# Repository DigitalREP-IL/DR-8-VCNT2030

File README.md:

This sensor board is designed around the Vishay VCNT2030, a new Vertical Cavity Surface Emitting Laser (VCSEL) short range reflective sensor.

The current-related resistors were chosen following the Vishay application note for a long distance / low reflectivity scenario. Thus, for optimal performance the board should be supplied at 5V, although the Send input is buffered by a small MOSFET with a Vgs of 1.8V.

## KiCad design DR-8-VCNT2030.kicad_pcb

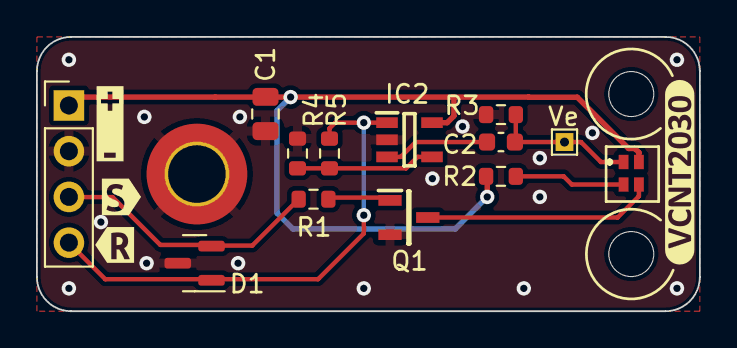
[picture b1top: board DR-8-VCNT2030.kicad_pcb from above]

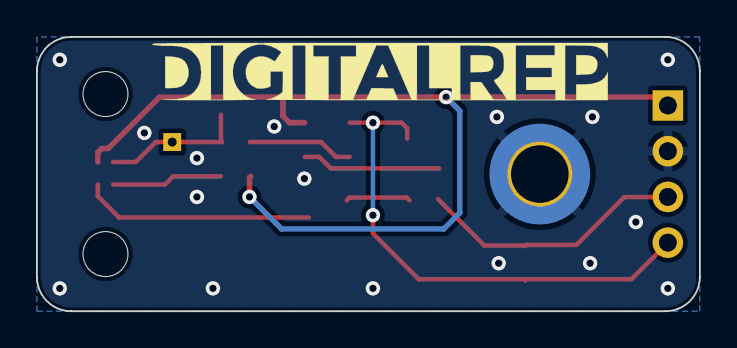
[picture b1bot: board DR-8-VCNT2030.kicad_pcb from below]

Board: 2 copper layers, 36.8 x 15.2 mm, 20 parts (2 on the bottom side), 10 nets.

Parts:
C1: C; C_0805_2012Metric
C2: C; C_0603_1608Metric
D1: SP0502BAHT; SOT-23
H1: MountingHole_Pad; MountingHole_3.2mm_M3_DIN965_Pad_TopBottom
IC1: VCNT2030
IC2: MIC6211YM5-TR; SOT95P280X145-5N
J1: Conn_01x04; PinHeader_1x04_P2.54mm_Vertical
LOGO1: Digital; digital
LOGO2: Rep; repword_soldermask
Q1: SI2302CDS-T1-GE3; SOT95P237X112-3N
R1: 100; R_0603_1608Metric
R2, R3, R4, R5: R_US; R_0603_1608Metric
TP1: Ve; TestPoint_THTPad_1.0x1.0mm_Drill0.5mm
kibuzzard-64F8F02C: G***; kibuzzard-64F8F02C
kibuzzard-64F8F03C: G***; kibuzzard-64F8F03C
kibuzzard-64F8F007: G***; kibuzzard-64F8F007
kibuzzard-64F9C572: G***; kibuzzard-64F9C572

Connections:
/S: D1.2 (K), J1.3, R1.1
/VCSEL_A: IC1.2, R2.2
/VCSEL_C: IC1.3, Q1.3
/Ve: C2.1, IC1.1, R3.1, TP1.1
GND: C1.2, D1.3 (A), H1.1, IC2.2 (V-), J1.2, Q1.2, R3.2, R4.2
unnamed: C2.2, IC2.3 (+)
unnamed: IC2.4 (-), R4.1, R5.1
unnamed: Q1.1, R1.2
R: D1.1 (K), IC2.1 (OUT), J1.4, R5.2
VCC: C1.1, IC1.4, IC2.5 (V+), J1.1, R2.1
